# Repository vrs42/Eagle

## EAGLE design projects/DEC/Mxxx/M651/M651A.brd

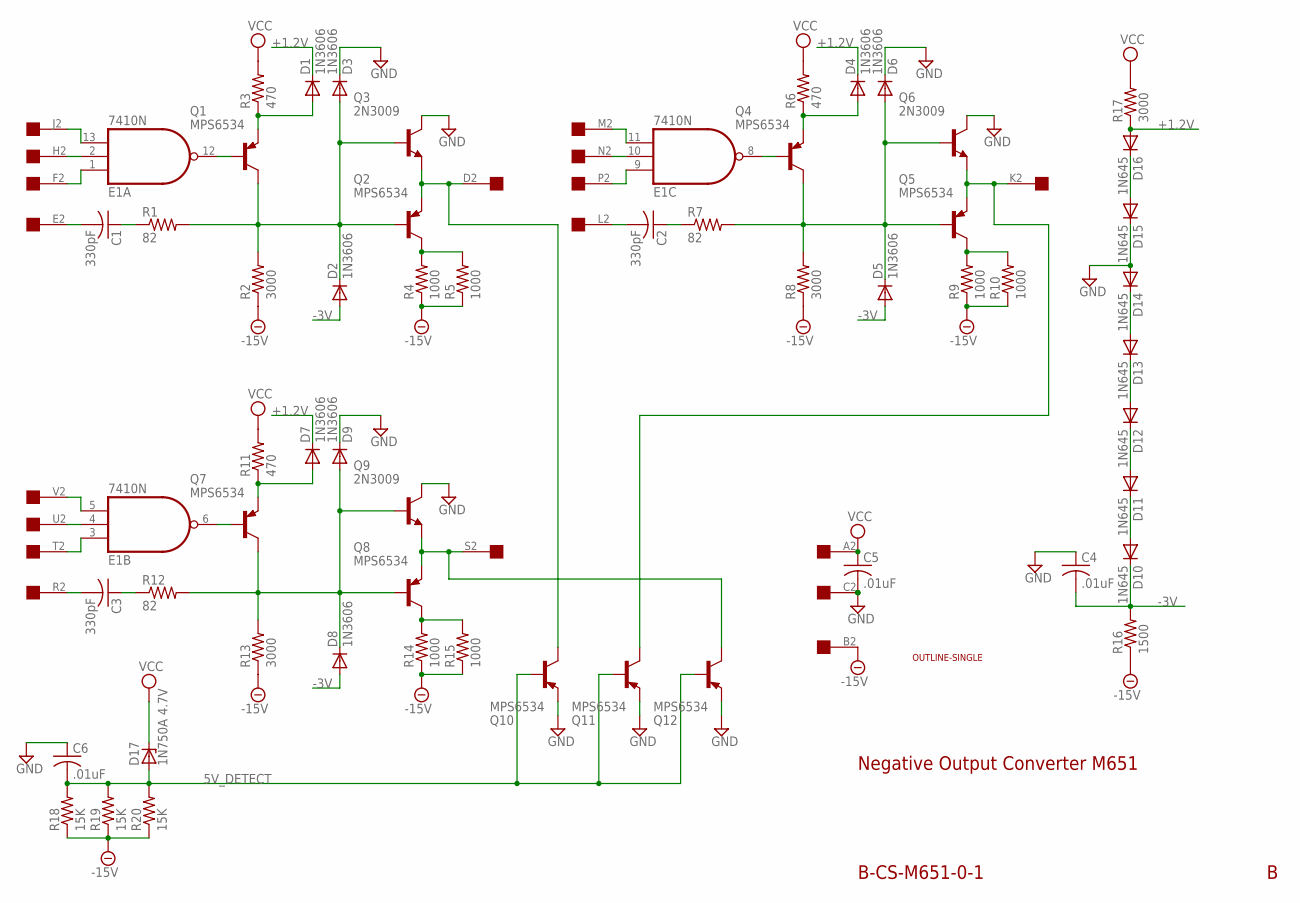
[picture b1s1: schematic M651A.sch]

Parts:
C1, C2, C3: 330pF; C050-025X075
C4, C5, C6: .01uF; C050-025X075
D1, D2, D3, D4, D5, D6, D7, D8, D9: 1N3606; DO35-10
D10, D11, D12, D13, D14, D15, D16: 1N645; DO35-10
D17: 1N750A 4.7V; DO35Z10
E1: 7410N; DIL14
Q1, Q2, Q4, Q5, Q7, Q8, Q10, Q11, Q12: MPS6534; TO39
Q3, Q6, Q9: 2N3009; TO5
R1, R7, R12: 82; 0207/10
R2, R8, R13, R17: 3000; 0207/10
R3, R6, R11: 470; 0207/10
R4, R5, R9, R10, R14, R15: 1000; 0207/10
R16: 1500; 0207/10
R18, R19, R20: 15K; 0207/10
U$1: OUTLINE-SINGLE; SINGLE
U$3: EDGE-1; EDGE-CON1

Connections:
5V_DETECT: C6.2, D17.A, Q10.2 (B), Q11.2 (B), Q12.2 (B), R18.2, R19.2, R20.2
+1.2V: D1.C, D4.C, D7.C, D16.A, R17.1
-3V: C4.2, D2.A, D5.A, D8.A, D10.C, R16.2
-15V: R2.1, R4.1, R5.1, R8.1, R9.1, R10.1, R13.1, R14.1, R15.1, R16.1, R18.1, R19.1, R20.1, U$3.B2
GND: C4.1, C5.2, C6.1, D3.C, D6.C, D9.C, D14.A, D15.C, E1.7 (GND), Q3.3 (C), Q6.3 (C), Q9.3 (C), Q10.1 (E), Q11.1 (E), Q12.1 (E), U$3.C2
unnamed: E1.2 (I1), U$3.H2
unnamed: C1.2, U$3.E2
unnamed: C1.1, R1.1
unnamed: E1.12 (O), Q1.2 (B)
unnamed: D1.A, Q1.1 (E), R3.1
unnamed: D2.C, D3.A, Q1.3 (C), Q2.2 (B), Q3.2 (B), R1.2, R2.2
unnamed: Q2.1 (E), Q3.1 (E), Q10.3 (C), U$3.D2
unnamed: Q2.3 (C), R4.2, R5.2
unnamed: E1.9 (I0), U$3.P2
unnamed: E1.11 (I2), U$3.M2
unnamed: E1.10 (I1), U$3.N2
unnamed: E1.8 (O), Q4.2 (B)
unnamed: D4.A, Q4.1 (E), R6.1
unnamed: E1.1 (I0), U$3.F2
unnamed: E1.13 (I2), U$3.J2
unnamed: C2.2, U$3.L2
unnamed: C2.1, R7.1
unnamed: D5.C, D6.A, Q4.3 (C), Q5.2 (B), Q6.2 (B), R7.2, R8.2
unnamed: Q5.1 (E), Q6.1 (E), Q11.3 (C), U$3.K2
unnamed: Q5.3 (C), R9.2, R10.2
unnamed: E1.3 (I0), U$3.T2
unnamed: E1.5 (I2), U$3.V2
unnamed: E1.4 (I1), U$3.U2
unnamed: E1.6 (O), Q7.2 (B)
unnamed: D7.A, Q7.1 (E), R11.1
unnamed: C3.2, U$3.R2
unnamed: C3.1, R12.1
unnamed: D8.C, D9.A, Q7.3 (C), Q8.2 (B), Q9.2 (B), R12.2, R13.2
unnamed: Q8.1 (E), Q9.1 (E), Q12.3 (C), U$3.S2
unnamed: Q8.3 (C), R14.2, R15.2
unnamed: D10.A, D11.C
unnamed: D11.A, D12.C
unnamed: D12.A, D13.C
unnamed: D13.A, D14.C
unnamed: D15.A, D16.C
VCC: C5.1, D17.C, E1.14 (VCC), R3.2, R6.2, R11.2, R17.2, U$3.A2

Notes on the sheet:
Negative Output Converter M651
B-CS-M651-0-1

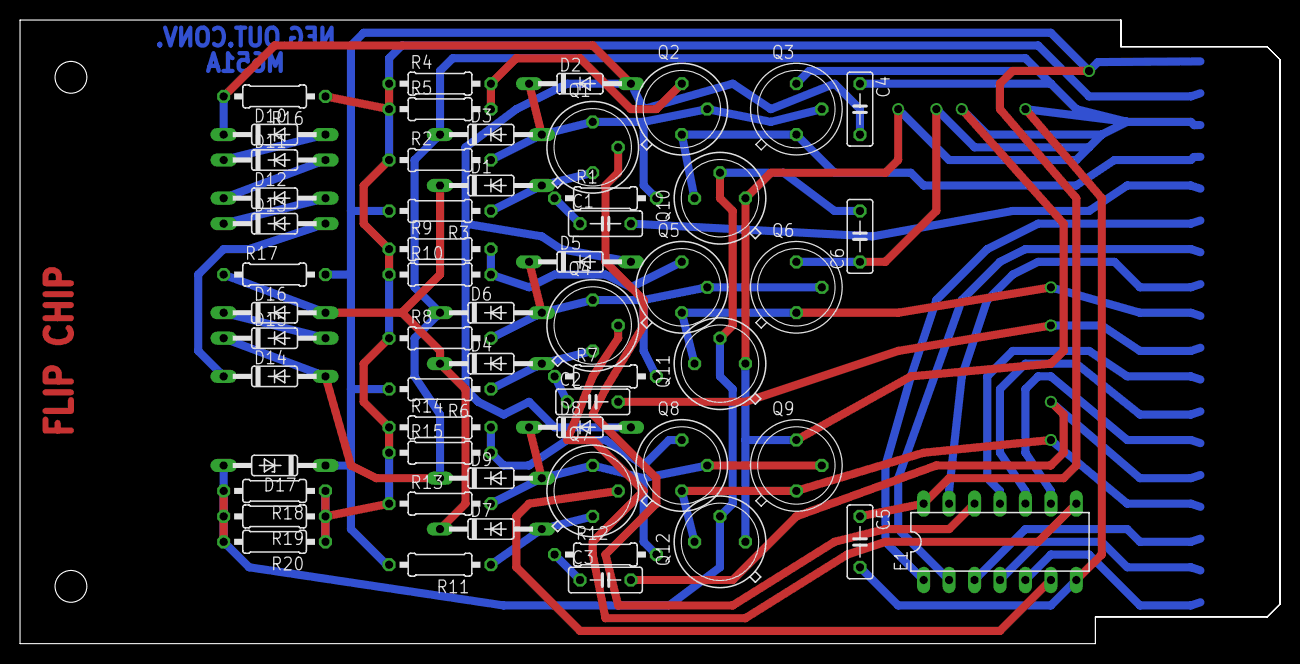
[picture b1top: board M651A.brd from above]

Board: 2 copper layers, 125.7 x 62.2 mm, 59 parts (0 on the bottom side), 41 nets.

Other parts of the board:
U$2: FLIPCHIP

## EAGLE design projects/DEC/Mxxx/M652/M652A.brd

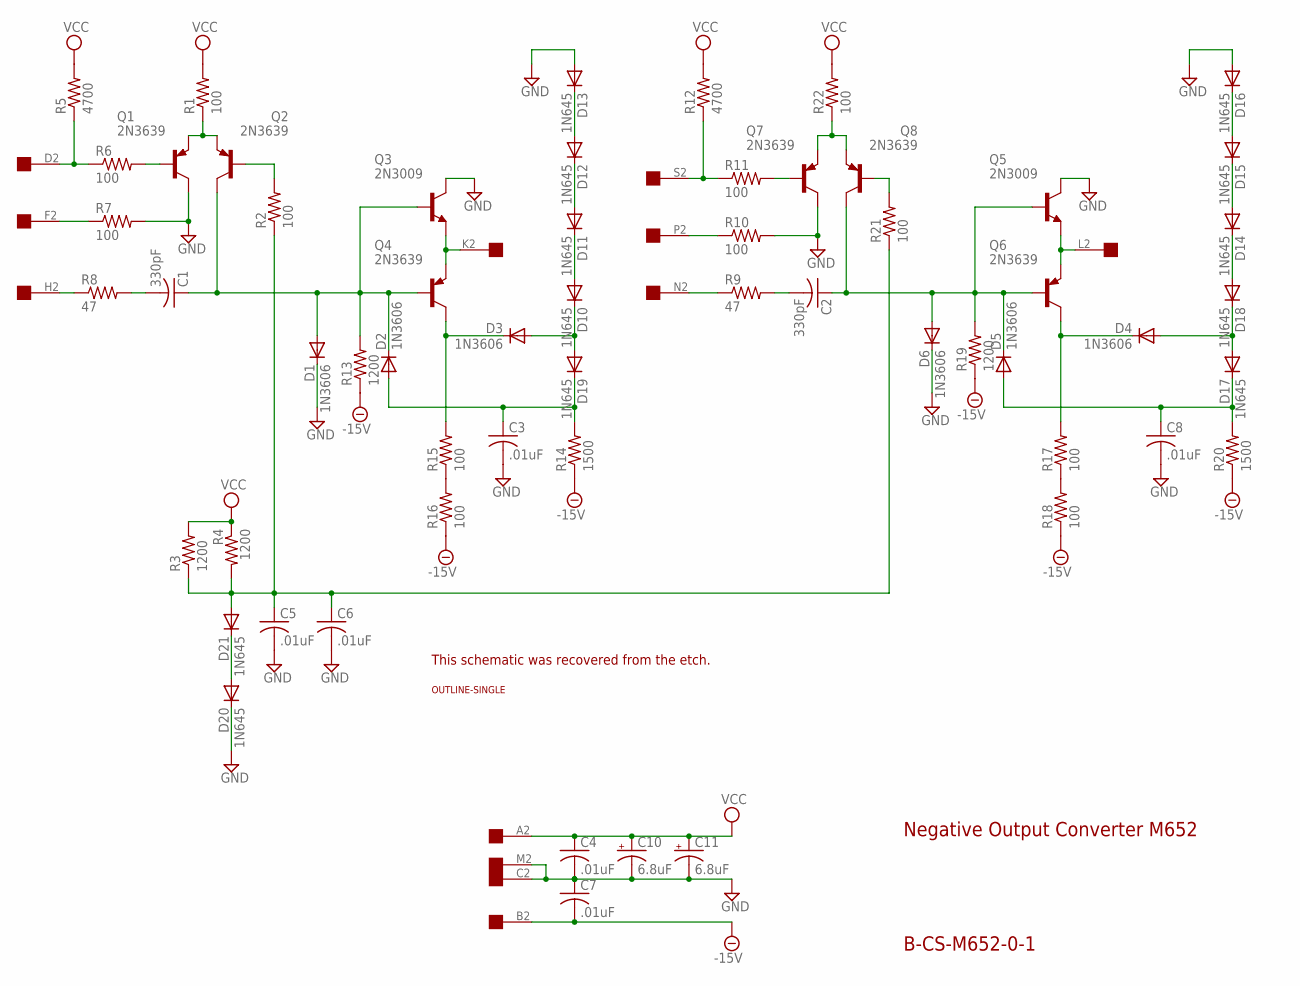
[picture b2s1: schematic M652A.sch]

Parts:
C1, C2: 330pF; C150-054X183
C3, C4, C5, C6, C7, C8: .01uF; C050-025X075
C10, C11: 6.8uF; E12-4
D1, D2, D3, D4, D5, D6: 1N3606; DO35-10
D10, D11, D12, D13, D14, D15, D16, D17, D18, D19, D20, D21: 1N645; DO35-10
Q1, Q2, Q4, Q6, Q7, Q8: 2N3639; TO39
Q3, Q5: 2N3009; TO5
R1, R2, R6, R7, R10, R11, R15, R16, R17, R18, R21, R22: 100; 0207/10
R3, R4, R13, R19: 1200; 0207/10
R5, R12: 4700; 0207/10
R8, R9: 47; 0207/10
R14, R20: 1500; 0207/10
U$1: OUTLINE-SINGLE; SINGLE
U$3: EDGE-1; EDGE-CON1

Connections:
-15V: C7.2, R13.1, R14.1, R16.1, R18.1, R19.1, R20.1, U$3.B2
GND: C3.2, C4.2, C5.2, C6.2, C7.1, C8.2, C10.-, C11.-, D1.C, D6.C, D13.A, D16.A, D20.C, Q1.3 (C), Q3.3 (C), Q5.3 (C), Q7.3 (C), R7.2, R10.2, U$3.C2, U$3.M2
unnamed: R5.1, R6.1, U$3.D2
unnamed: Q1.2 (B), R6.2
unnamed: Q1.1 (E), Q2.1 (E), R1.1
unnamed: R7.1, U$3.F2
unnamed: R8.1, U$3.H2
unnamed: C1.2, R8.2
unnamed: R15.1, R16.2
unnamed: Q3.1 (E), Q4.1 (E), U$3.K2
unnamed: Q5.1 (E), Q6.1 (E), U$3.L2
unnamed: C2.1, D5.C, D6.A, Q5.2 (B), Q6.2 (B), Q8.3 (C), R19.2
unnamed: C1.1, D1.A, D2.C, Q2.3 (C), Q3.2 (B), Q4.2 (B), R13.2
unnamed: Q7.1 (E), Q8.1 (E), R22.1
unnamed: Q7.2 (B), R11.2
unnamed: R11.1, R12.1, U$3.S2
unnamed: R9.1, U$3.N2
unnamed: R10.1, U$3.P2
unnamed: C5.1, C6.1, D21.A, R2.1, R3.1, R4.2, R21.1
unnamed: C2.2, R9.2
unnamed: D12.A, D13.C
unnamed: D15.A, D16.C
unnamed: D11.A, D12.C
unnamed: D14.A, D15.C
unnamed: D10.A, D11.C
unnamed: D14.C, D18.A
unnamed: C3.1, D2.A, D19.C, R14.2
unnamed: D3.A, D10.C, D19.A
unnamed: D4.A, D17.A, D18.C
unnamed: C8.1, D5.A, D17.C, R20.2
unnamed: D3.C, Q4.3 (C), R15.2
unnamed: D20.A, D21.C
unnamed: Q2.2 (B), R2.2
unnamed: Q8.2 (B), R21.2
unnamed: R17.1, R18.2
unnamed: D4.C, Q6.3 (C), R17.2
VCC: C4.1, C10.+, C11.+, R1.2, R3.2, R4.1, R5.2, R12.2, R22.2, U$3.A2

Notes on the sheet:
Negative Output Converter M652
B-CS-M652-0-1
This schematic was recovered from the etch.

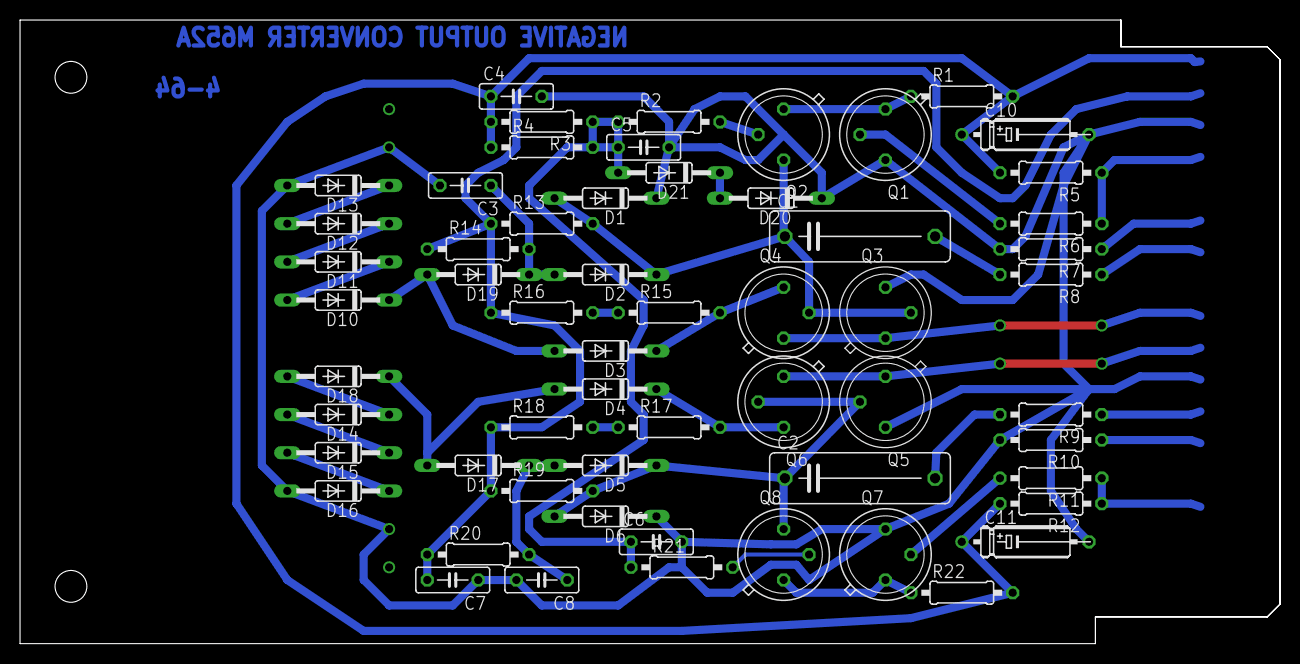
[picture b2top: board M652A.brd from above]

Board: 2 copper layers, 125.7 x 62.2 mm, 60 parts (0 on the bottom side), 37 nets.

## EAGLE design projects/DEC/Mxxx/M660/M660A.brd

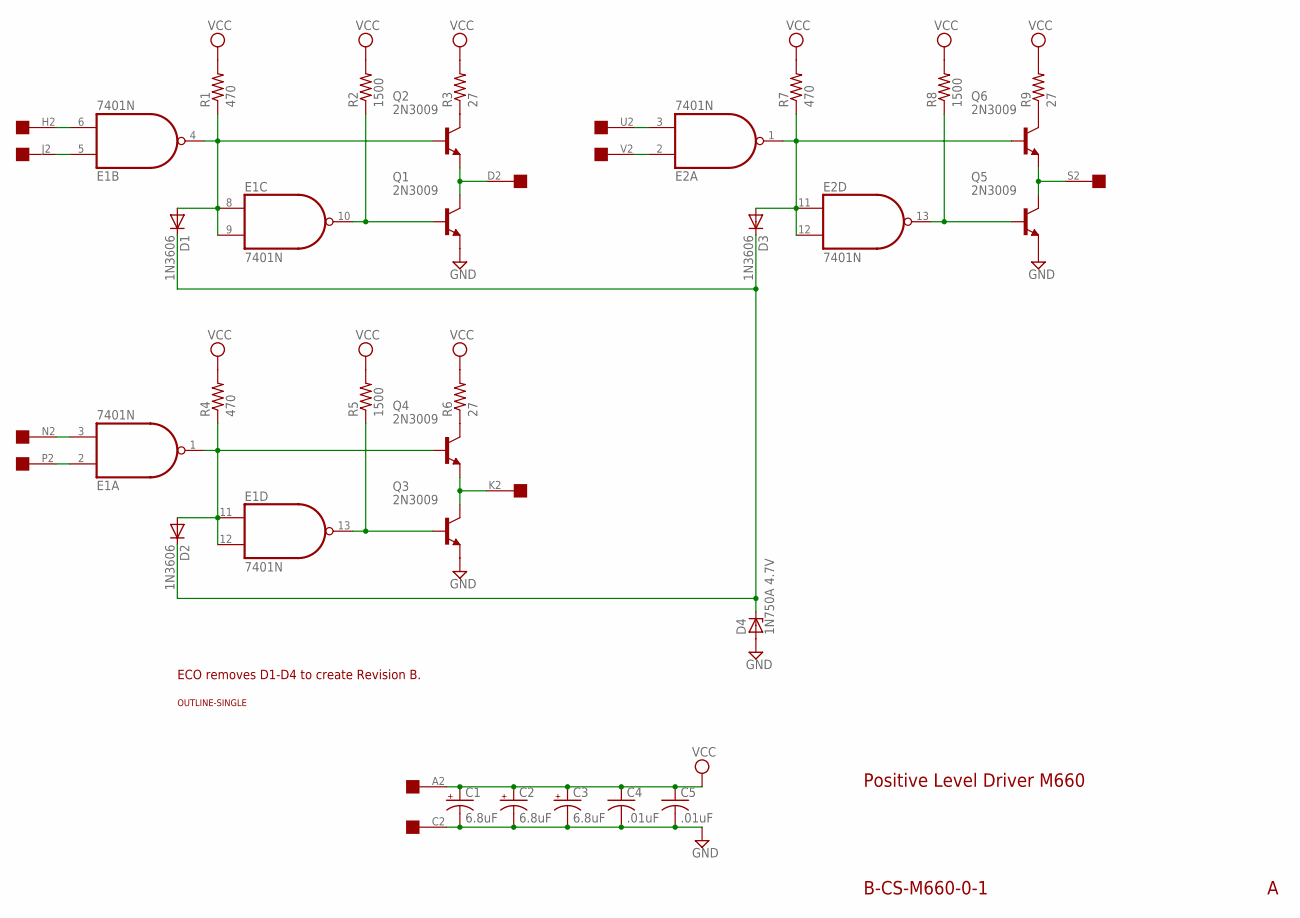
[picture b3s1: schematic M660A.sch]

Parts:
C1, C2, C3: 6.8uF; E15-5
C4, C5: .01uF; C050-025X075
D1, D2, D3: 1N3606; DO35-10
D4: 1N750A 4.7V; DO35Z10
E1, E2: 7401N; DIL14
Q1, Q2, Q3, Q4, Q5, Q6: 2N3009; TO5
R1, R4, R7: 470; 0207/10
R2, R5, R8: 1500; 0207/10
R3, R6, R9: 27; 0411/15
U$1: OUTLINE-SINGLE; SINGLE
U$3: EDGE-1; EDGE-CON1

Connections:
GND: C1.-, C2.-, C3.-, C4.2, C5.2, D4.A, E1.7 (GND), E2.7 (GND), Q1.1 (E), Q3.1 (E), Q5.1 (E), U$3.C2
unnamed: E1.5 (I0), U$3.J2
unnamed: E1.6 (I1), U$3.H2
unnamed: D1.A, E1.4 (O), E1.8 (I0), E1.9 (I1), Q2.2 (B), R1.1
unnamed: E1.10 (O), Q1.2 (B), R2.1
unnamed: Q2.3 (C), R3.1
unnamed: Q1.3 (C), Q2.1 (E), U$3.D2
unnamed: E1.2 (I0), U$3.P2
unnamed: E1.3 (I1), U$3.N2
unnamed: D2.A, E1.1 (O), E1.11 (I0), E1.12 (I1), Q4.2 (B), R4.1
unnamed: E1.13 (O), Q3.2 (B), R5.1
unnamed: Q4.3 (C), R6.1
unnamed: Q3.3 (C), Q4.1 (E), U$3.K2
unnamed: E2.2 (I0), U$3.V2
unnamed: E2.3 (I1), U$3.U2
unnamed: D3.A, E2.1 (O), E2.11 (I0), E2.12 (I1), Q6.2 (B), R7.1
unnamed: E2.13 (O), Q5.2 (B), R8.1
unnamed: Q6.3 (C), R9.1
unnamed: Q5.3 (C), Q6.1 (E), U$3.S2
unnamed: D1.C, D2.C, D3.C, D4.C
VCC: C1.+, C2.+, C3.+, C4.1, C5.1, E1.14 (VCC), E2.14 (VCC), R1.2, R2.2, R3.2, R4.2, R5.2, R6.2, R7.2, R8.2, R9.2, U$3.A2

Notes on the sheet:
Positive Level Driver M660
B-CS-M660-0-1
ECO removes D1-D4 to create Revision B.

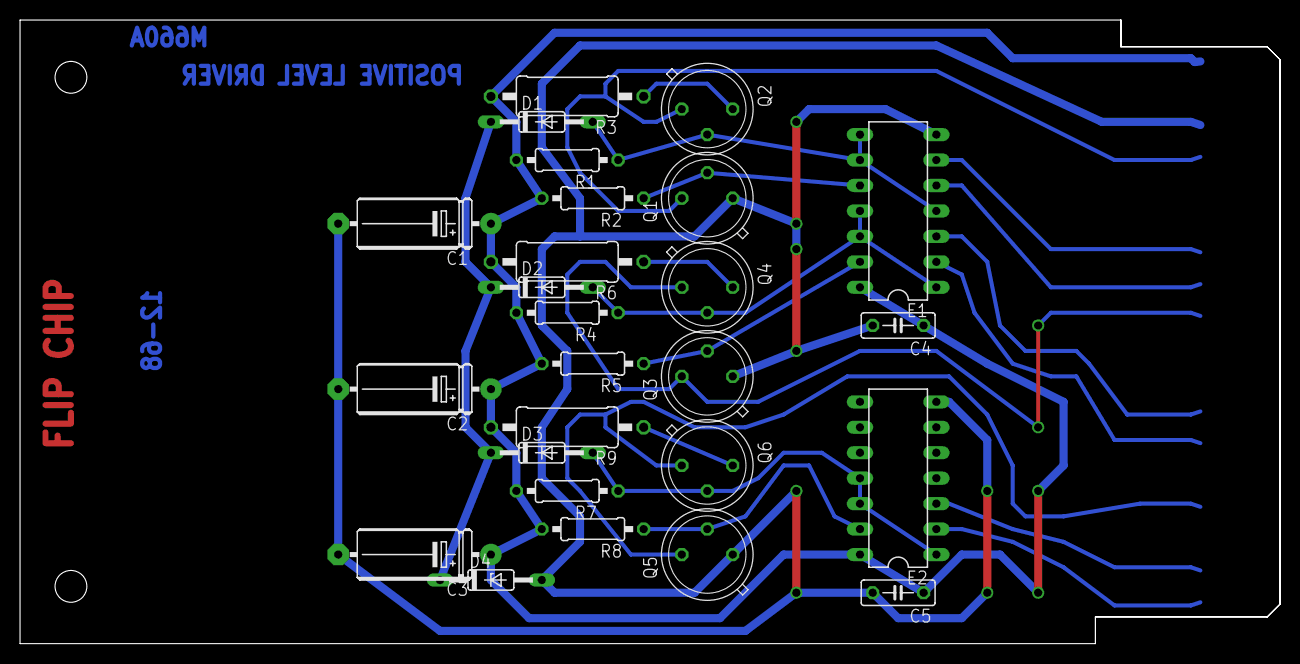
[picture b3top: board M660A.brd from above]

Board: 2 copper layers, 125.7 x 62.2 mm, 29 parts (0 on the bottom side), 21 nets.

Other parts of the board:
U$2: FLIPCHIP
